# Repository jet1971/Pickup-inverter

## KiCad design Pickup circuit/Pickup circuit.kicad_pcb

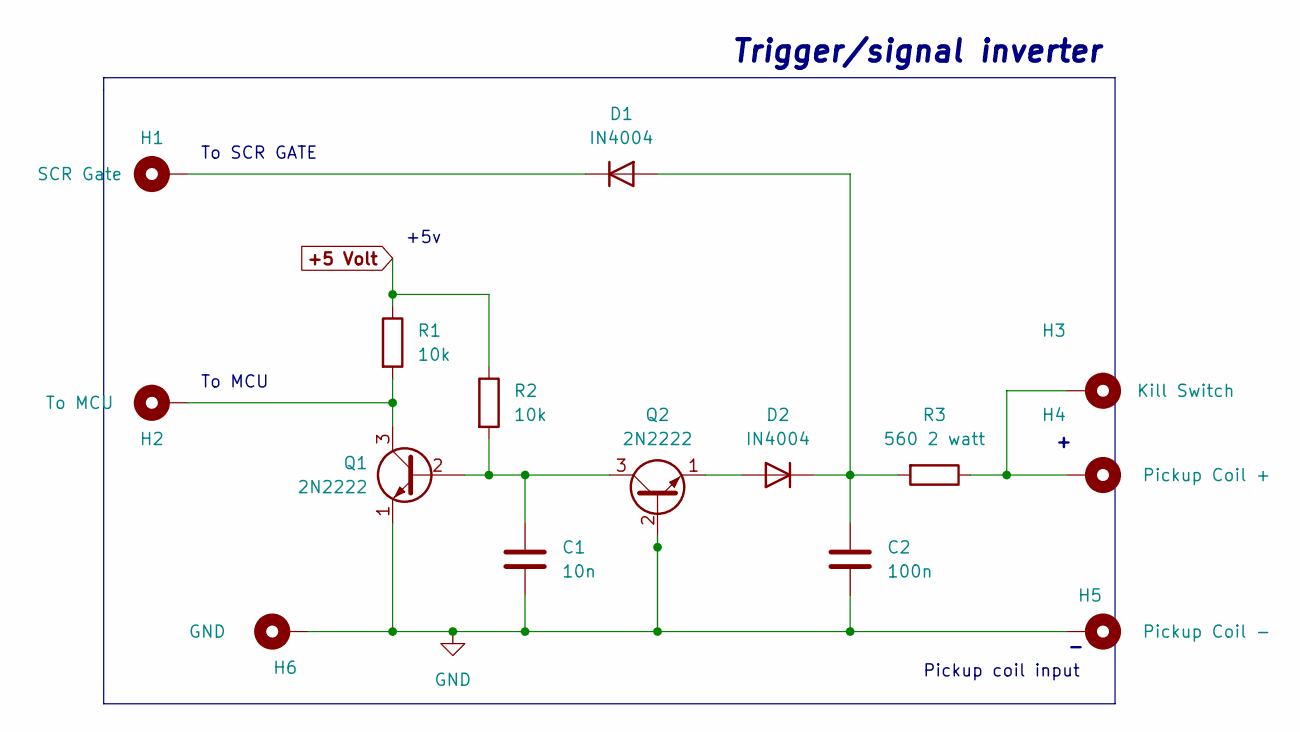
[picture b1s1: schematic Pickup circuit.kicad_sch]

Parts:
C1: 10n; C_Disc_D6.0mm_W2.5mm_P5.00mm
C2: 100n; C_Disc_D6.0mm_W2.5mm_P5.00mm
D1, D2: IN4004; D_DO-41_SOD81_P10.16mm_Horizontal
H1: SCR Gate; MountingHole_2.2mm_M2_Pad_TopBottom
H2: To MCU; MountingHole_2.2mm_M2_Pad_TopBottom
H3: Kill Switch; MountingHole_2.2mm_M2_Pad_TopBottom
H4: Pickup Coil +; MountingHole_2.2mm_M2_Pad_TopBottom
H5: Pickup Coil -; MountingHole_2.2mm_M2_Pad_TopBottom
H6: GND; MountingHole_2.2mm_M2_Pad_TopBottom
Q1, Q2: 2N2222; TO-92_Inline
R1, R2: 10k; R_Axial_DIN0207_L6.3mm_D2.5mm_P7.62mm_Horizontal
R3: 560 2 watt; R_Axial_DIN0516_L15.5mm_D5.0mm_P20.32mm_Horizontal

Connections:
+5 Volt: R1.1, R2.1
GND: C1.2, C2.2, H5.1, H6.1, Q1.1 (E), Q2.2 (B)
unnamed: C1.1, Q1.2 (B), Q2.3 (C), R2.2
unnamed: C2.1, D1.2 (A), D2.1 (K), R3.2
unnamed: D1.1 (K), H1.1
unnamed: D2.2 (A), Q2.1 (E)
unnamed: H2.1, Q1.3 (C), R1.2
unnamed: H3.1, H4.1, R3.1

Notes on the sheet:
Pickup coil input
Trigger/signal inverter
+5v
To SCR GATE
To MCU

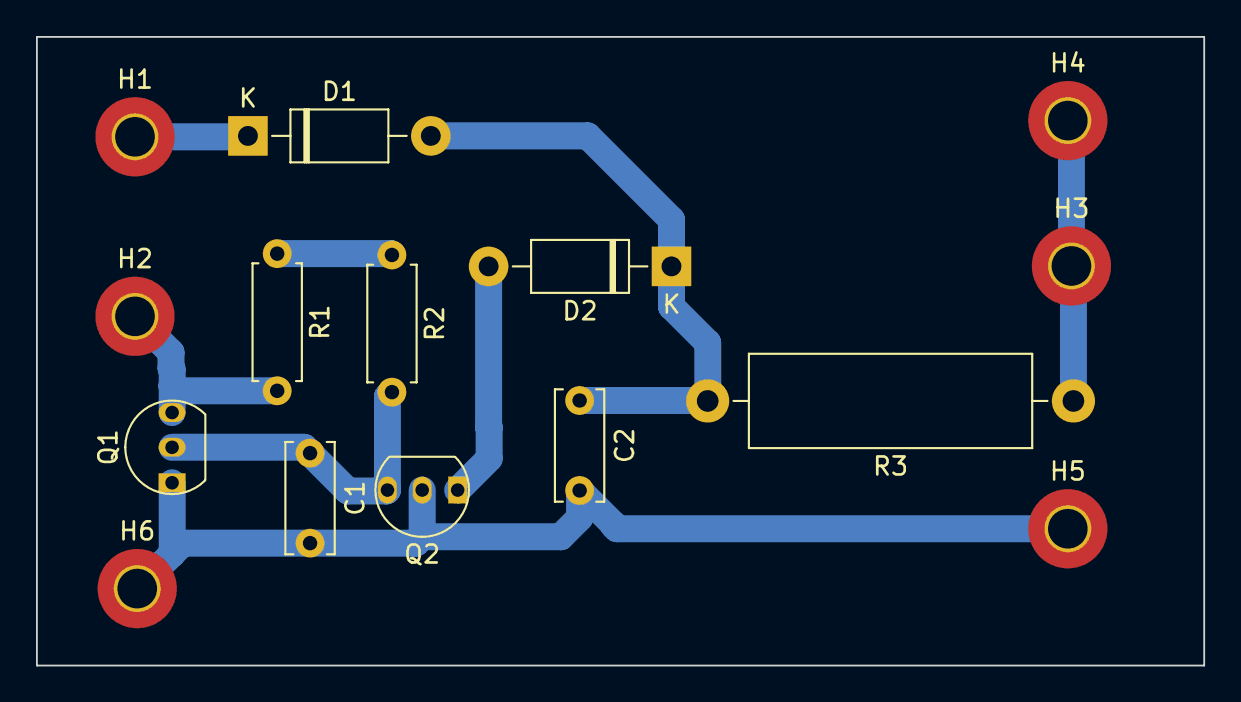
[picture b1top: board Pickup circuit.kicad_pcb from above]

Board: 2 copper layers, 64.8 x 34.9 mm, 15 parts (0 on the bottom side), 8 nets.

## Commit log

2022-09-04 Pickup coil inverter circuit
